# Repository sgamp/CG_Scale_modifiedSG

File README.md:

# CG_Scale_modifiedSG
Modified version of the CG scale project from Olkal

*using a 0.96" OLED Display
*using a button field (5 buttons) to enter a reference weight and to navigate
*writing reference results to EEPROM
More information can be found in the *.pdf

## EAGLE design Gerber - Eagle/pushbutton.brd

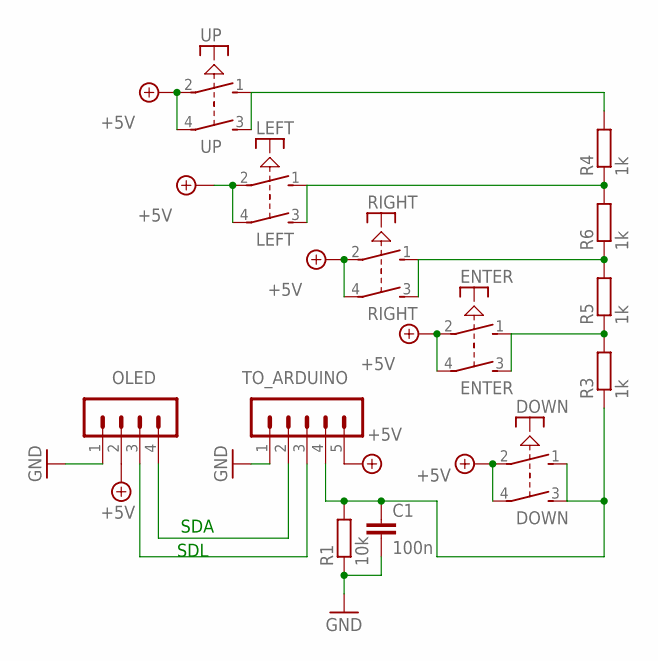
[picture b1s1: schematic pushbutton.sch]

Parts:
C1: 100n; C025-030X050
DOWN: PVA1R
ENTER: PVA1R
LEFT: PVA1R
OLED: MA04-1
R1: 10k; 0207/10
R3, R4, R5, R6: 1k; 0207/10
RIGHT: PVA1R
TO_ARDUINO: MA05-1
UP: PVA1R

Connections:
+5V: DOWN.2, DOWN.4, ENTER.2, ENTER.4, LEFT.2, LEFT.4, OLED.2, RIGHT.2, RIGHT.4, TO_ARDUINO.5, UP.2, UP.4
GND: C1.2, OLED.1, R1.1, TO_ARDUINO.1
unnamed: ENTER.1 (S), ENTER.3 (S), R3.2, R5.1
unnamed: R4.2, UP.1 (S), UP.3 (S)
unnamed: C1.1, DOWN.1 (S), DOWN.3 (S), R1.2, R3.1, TO_ARDUINO.4
unnamed: R5.2, R6.1, RIGHT.1 (S), RIGHT.3 (S)
unnamed: LEFT.1 (S), LEFT.3 (S), R4.1, R6.2
SCL: OLED.3, TO_ARDUINO.3
SDA: OLED.4, TO_ARDUINO.2

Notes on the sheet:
SDL
SDA

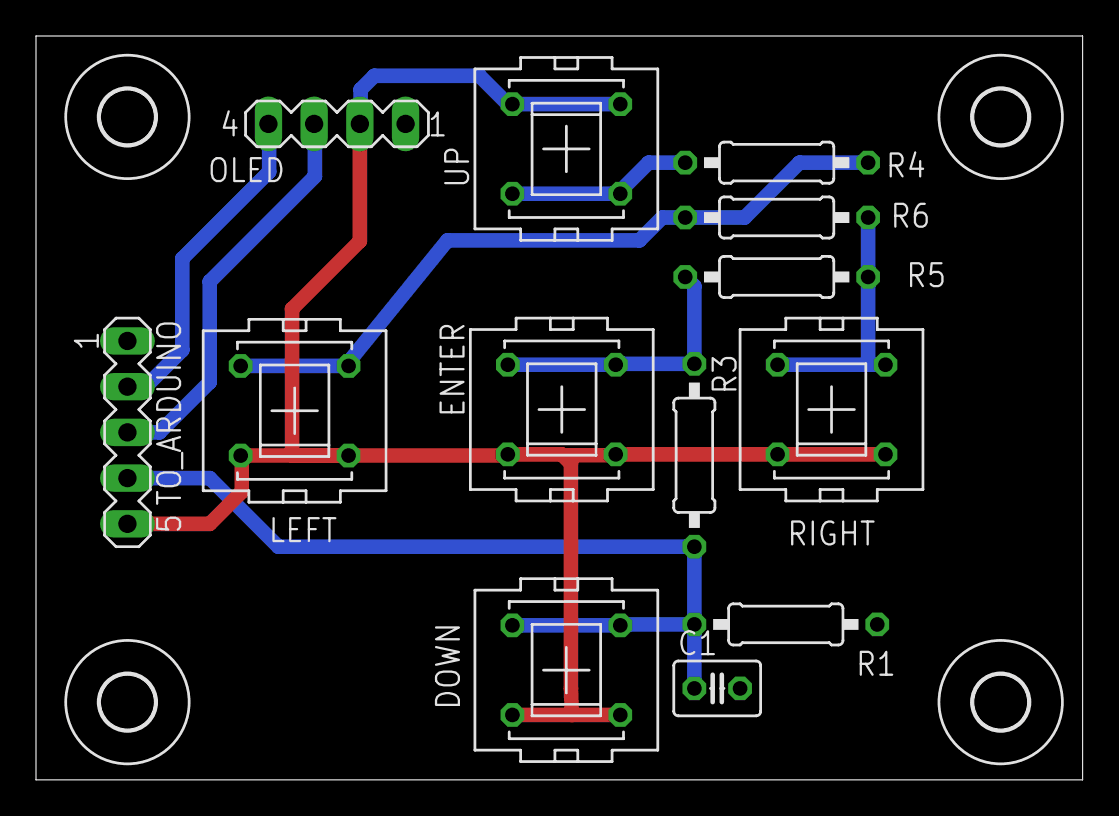
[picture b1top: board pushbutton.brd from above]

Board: 2 copper layers, 58.1 x 41.3 mm, 17 parts (0 on the bottom side), 9 nets.

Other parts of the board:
U$1, U$2, U$3, U$4: 3,0

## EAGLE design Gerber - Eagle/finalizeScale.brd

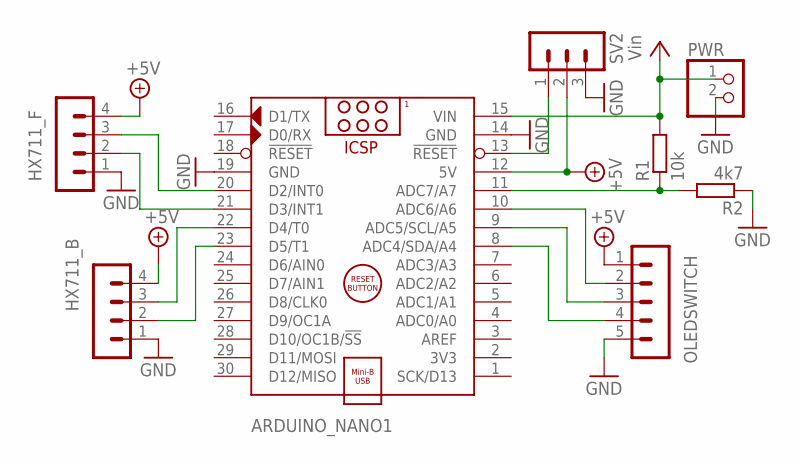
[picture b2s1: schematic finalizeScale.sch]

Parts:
ARDUINO_NANO1: ARDUINO_NANO
HX711_B, HX711_F: MA04-1
OLEDSWITCH: MA05-1
PWR: PINHD-1X2; 1X02
R1: 10k; 0207/10
R2: 4k7; 0207/10
SV2: MA03-1

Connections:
+5V: ARDUINO_NANO1.12 (5V), HX711_B.4, HX711_F.4, OLEDSWITCH.1, SV2.2
GND: ARDUINO_NANO1.14 (GND), ARDUINO_NANO1.19 (GND), HX711_B.1, HX711_F.1, OLEDSWITCH.5, PWR.2, R2.1, SV2.3
unnamed: ARDUINO_NANO1.8 (ADC4/SDA/A4), OLEDSWITCH.4
unnamed: ARDUINO_NANO1.9 (ADC5/SCL/A5), OLEDSWITCH.3
unnamed: ARDUINO_NANO1.11 (ADC7/A7), R1.1, R2.2
unnamed: ARDUINO_NANO1.21 (D3/INT1), HX711_F.2
unnamed: ARDUINO_NANO1.10 (ADC6/A6), OLEDSWITCH.2
unnamed: ARDUINO_NANO1.22 (D4/T0), HX711_B.3
unnamed: ARDUINO_NANO1.23 (D5/T1), HX711_B.2
unnamed: ARDUINO_NANO1.20 (D2/INT0), HX711_F.3
unnamed: ARDUINO_NANO1.13 (!RESET), SV2.1
VCC: ARDUINO_NANO1.15 (VIN), PWR.1, R1.2

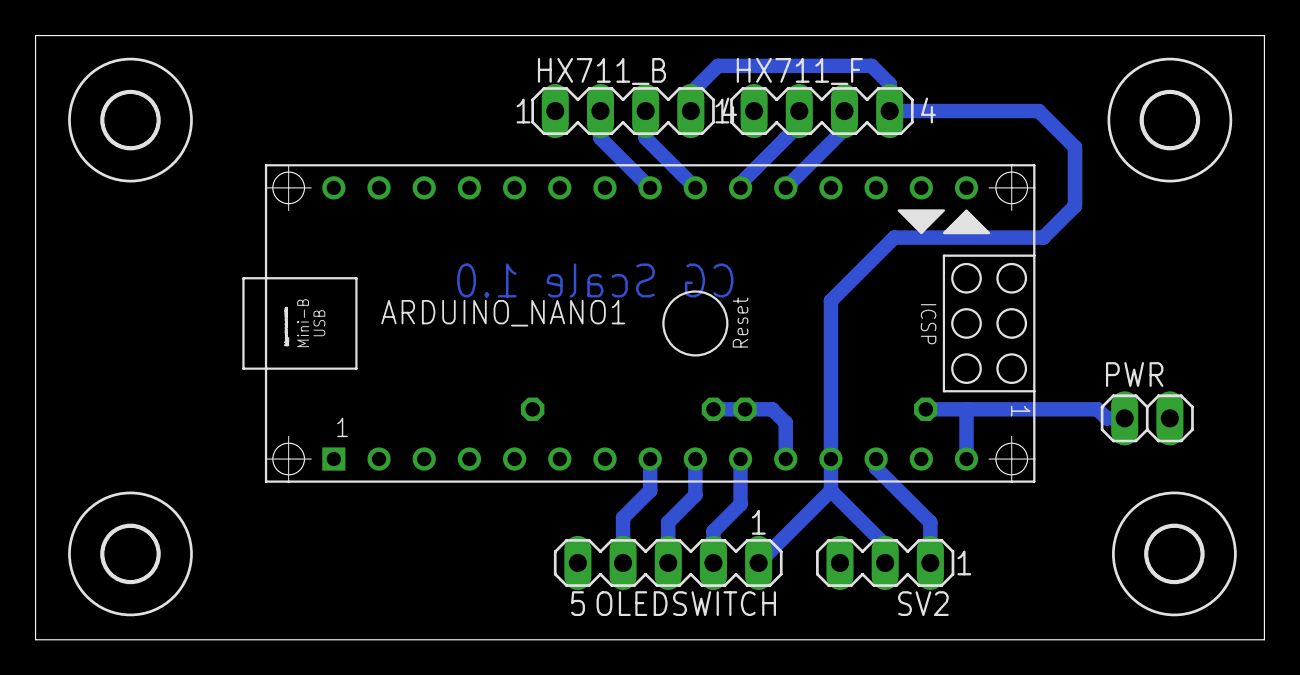
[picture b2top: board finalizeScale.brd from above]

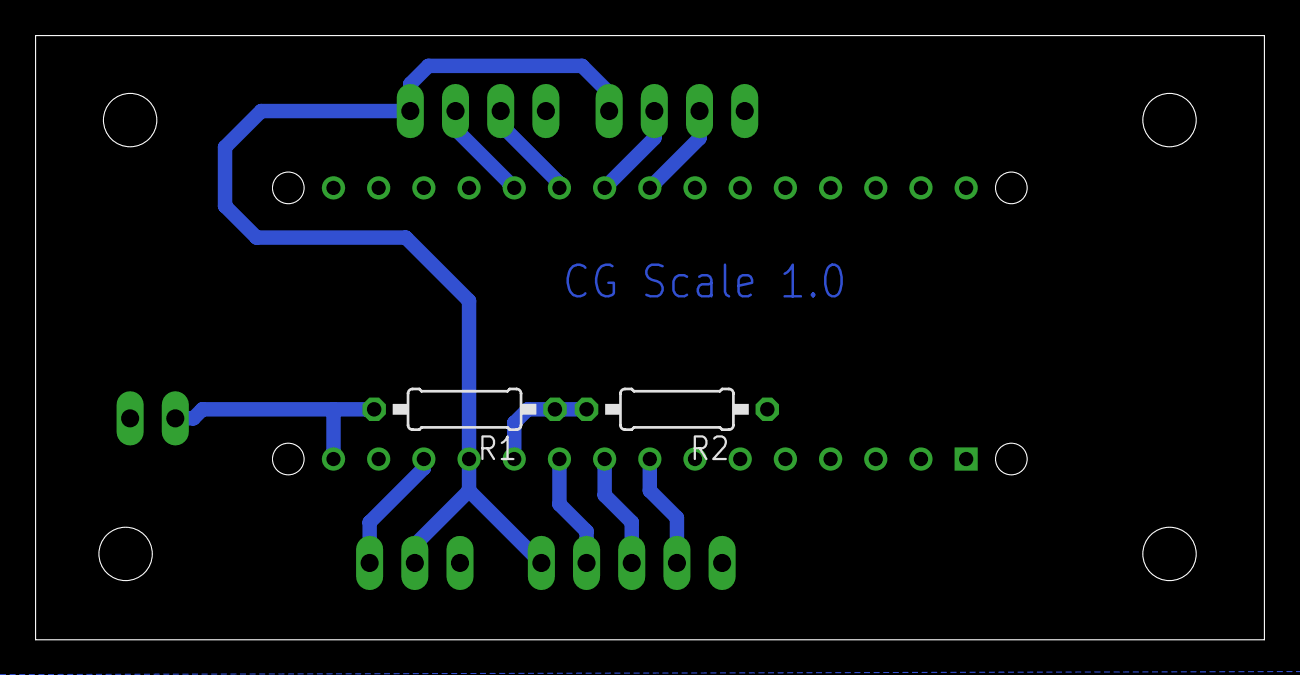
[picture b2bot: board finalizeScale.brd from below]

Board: 2 copper layers, 69.1 x 34.0 mm, 12 parts (2 on the bottom side), 12 nets.

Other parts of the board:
U$1, U$2, U$3, U$4: 3,0

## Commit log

2018-12-12 Create test
